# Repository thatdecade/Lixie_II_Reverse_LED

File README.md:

# Remix of Lixie II Open Hardware
Want to make your own Lixie II, but don't want to spend $$$$? You're in the right place. 

Based on the original work by Connor Nishijima: https://github.com/connornishijima/Lixie_II_OSHW

**Photo Album**
https://photos.app.goo.gl/PVswYqP2KvHP66T27

## Remix Notes
- PCB redrawn with a new BOM, using reverse mount LEDs. https://www.adafruit.com/product/4960
  - Loosely based on Adafruit's RGB NeoKey https://www.adafruit.com/product/5157
  - One capacitor per LED
  - Transmission resistors for stable data
- EPS files for lasercutting were converted to DXF.
- Laser Cut files have been redrawn for smaller runs.  
  - Ordering one set = One Digit of the Display
  - Ponoko wil auto-panelize larger orders together.
  - Be sure to read https://help.ponoko.com/en/articles/4405518-getting-started-with-ponoko
- 3D Printed versions of some of the lasercut files

|Filename|Supplier|Material|Thickness|
| ----------- | ----------- | ----------- | ----------- |
|BASEx2.dxf|Ponoko|Black Melamine MDF|6.4|
|NUM0-9.dxf|Ponoko|Clear Acrylic|1.5|
|DECIMAL.dxf|Ponoko|Gray Translucent Acrylic|3|
|LIGHTFILTER.dxf|Ponoko|6061-T6 Aluminum|1|

- LixieII_Price_Calculator.xlsx calculates the cost (including electronics) based on how many you would like to make.  
Here are some BOM estimates as of Oct 28, 2022:

|QTY|Total Cost|Cost Each|
| ----------- | ----------- | ----------- |
|1|$166|$166|
|2|$233|$117|
|4|$255|$64|
|8|$392|$49|
|10|$446|$45|
|16|$665|$42|
|32|$1250|$39|
|200|$4740|$24|

## Todo

- Convert Lightplate into pcb gerbers for cheaper cutting

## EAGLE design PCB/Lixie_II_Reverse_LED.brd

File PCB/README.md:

Here you will find the files for the PCB.  

To order the PCBs pre-assembled, visit [pcbshopper](https://pcbshopper.com/) and click the Assembly tab.  Then you can fill out the form and compare pricing from different assemblers.

## Files for assembly:

* Lixie_II_Reverse_LED_GERBERS.zip
* Lixie_II_Reverse_LED_BOM.xlsx
* Lixie_II_Reverse_LED_PLACEMENT.xlsx

## Notes:

* If you don't have EagleCAD to open the .brd/.sch files, you can use the free version of Autodesk Fusion 360 and download Eagle Free.
* I use eagle to generate the .dxf files, ensuring alignment between the pcb and other layers.  

## Generating the DXF Files
Example for LIGHTFILTER.dxf
1. Open the the .brd file in eagle
1. View>Layer Settings: 
> * Select None
> * Select only the LIGHTFILTER/ENGRAVING layers
3. File>Export>DXF: 
> * Name the output file: LIGHTFILTER.dxf
> * Unselect Fill areas
> * Unselect Use wire widths
> * Set Units to mm
> * Press OK

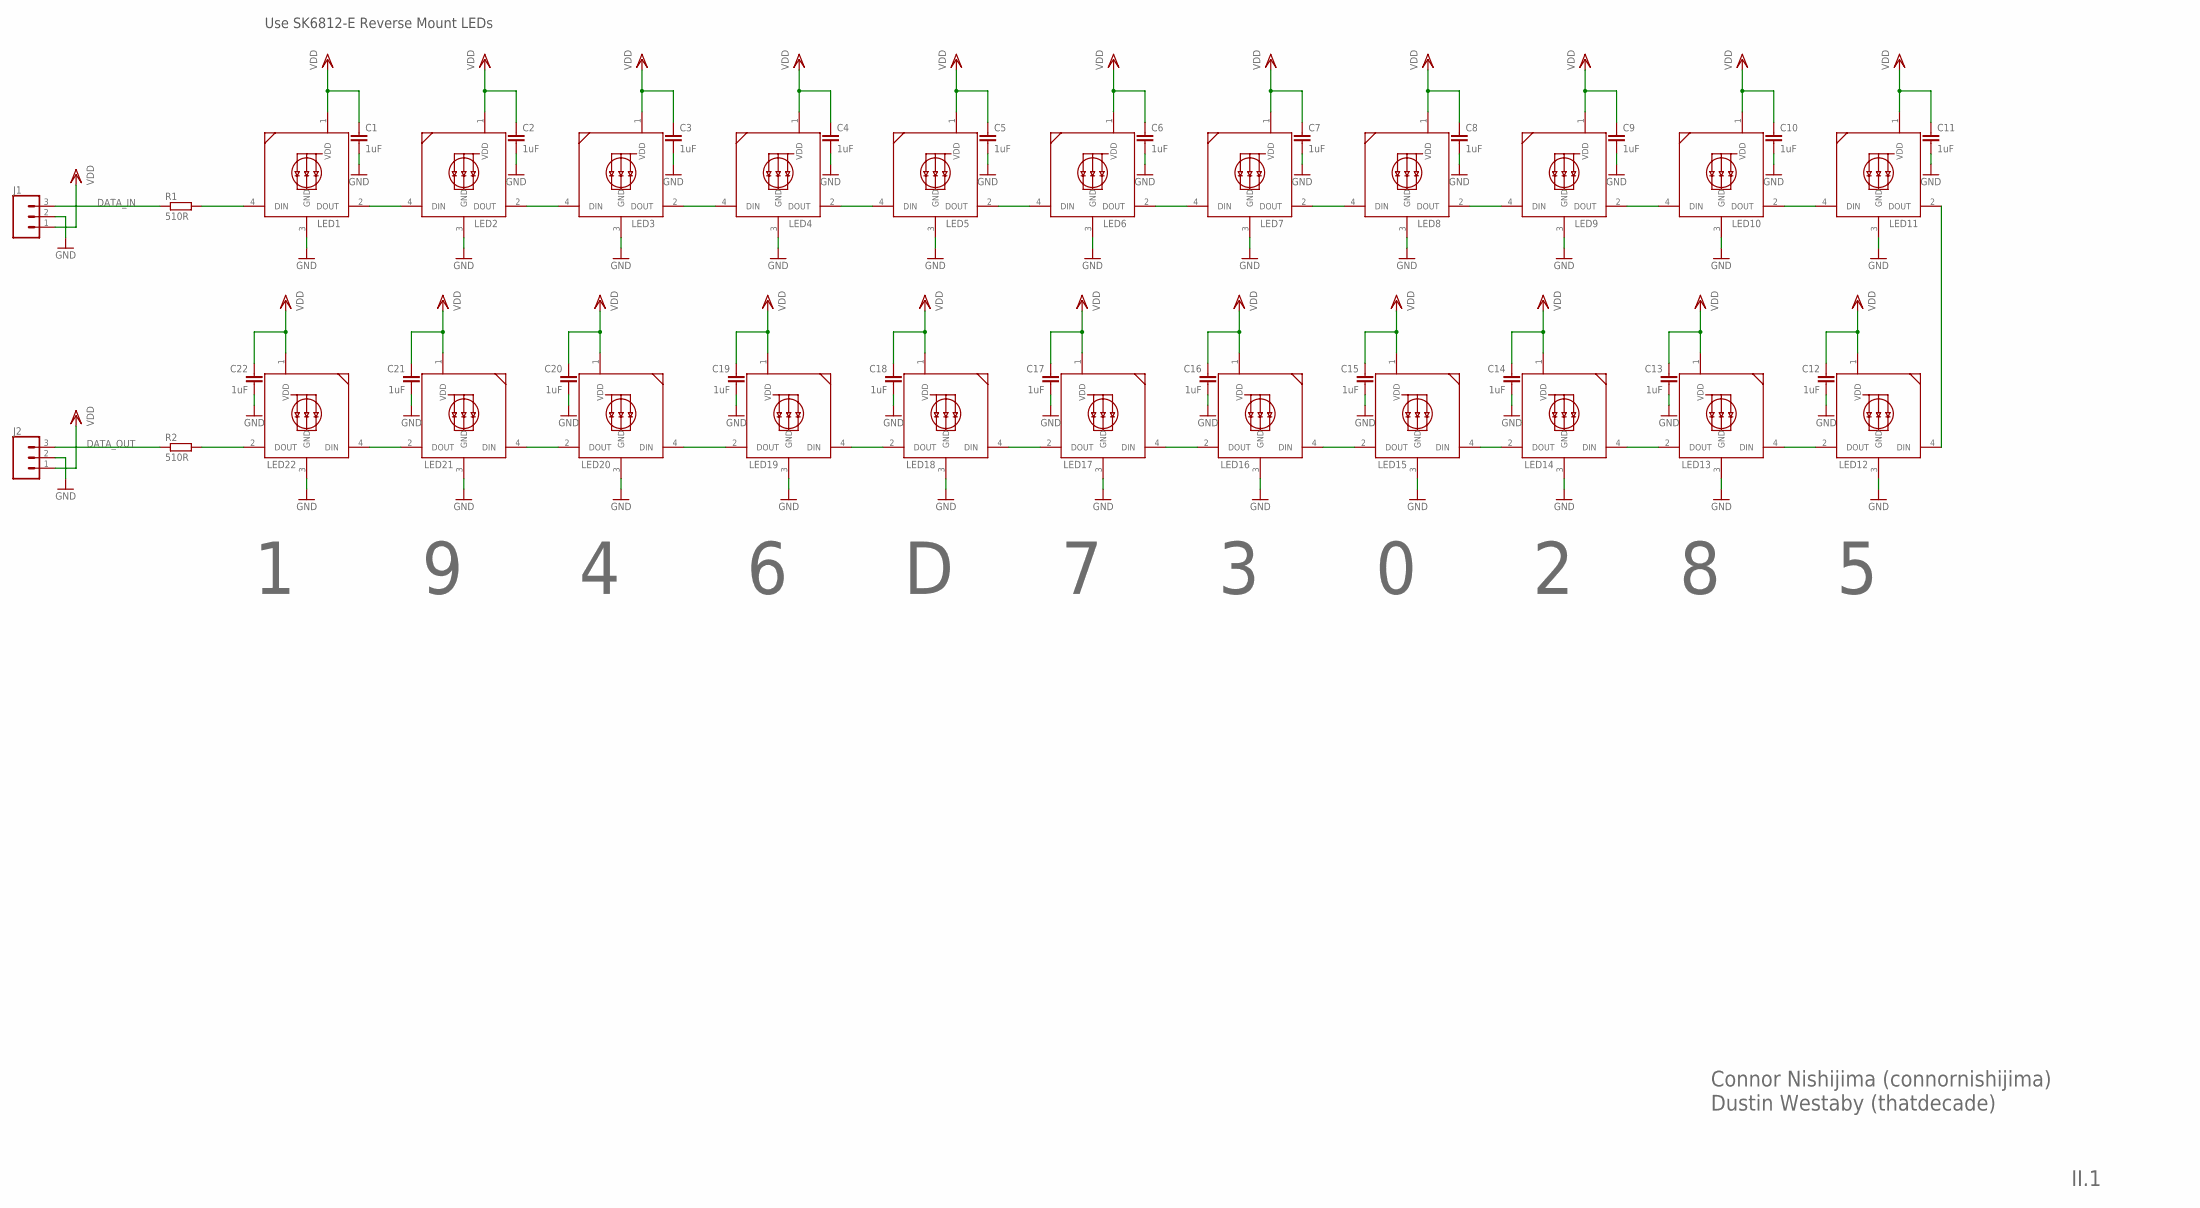
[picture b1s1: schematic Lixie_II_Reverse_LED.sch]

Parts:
C1, C2, C3, C4, C5, C6, C7, C8, C9, C10, C11, C12, C13, C14, C15, C16, C17, C18, C19, C20, C21, C22: 1uF; C0402
J1, J2: CONN_031X03_NO_SILK; 1X03_NO_SILK
LED1, LED2, LED3, LED4, LED5, LED6, LED7, LED8, LED9, LED10, LED11, LED12, LED13, LED14, LED15, LED16, LED17, LED18, LED19, LED20, LED21, LED22: SK6812MINI_REV; SK6812-E-SMD
R1, R2: 510R; R0402

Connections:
DATA_IN: J1.3, R1.1
DATA_OUT: J2.3, R2.1
GND: C1.2, C2.2, C3.2, C4.2, C5.2, C6.2, C7.2, C8.2, C9.2, C10.2, C11.2, C12.2, C13.2, C14.2, C15.2, C16.2, C17.2, C18.2, C19.2, C20.2, C21.2, C22.2, J1.2, J2.2, LED1.3 (GND), LED2.3 (GND), LED3.3 (GND), LED4.3 (GND), LED5.3 (GND), LED6.3 (GND), LED7.3 (GND), LED8.3 (GND), LED9.3 (GND), LED10.3 (GND), LED11.3 (GND), LED12.3 (GND), LED13.3 (GND), LED14.3 (GND), LED15.3 (GND), LED16.3 (GND), LED17.3 (GND), LED18.3 (GND), LED19.3 (GND), LED20.3 (GND), LED21.3 (GND), LED22.3 (GND)
unnamed: LED1.4 (DIN), R1.2
unnamed: LED11.2 (DOUT), LED12.4 (DIN)
unnamed: LED22.2 (DOUT), R2.2
unnamed: LED21.2 (DOUT), LED22.4 (DIN)
unnamed: LED20.2 (DOUT), LED21.4 (DIN)
unnamed: LED19.2 (DOUT), LED20.4 (DIN)
unnamed: LED18.2 (DOUT), LED19.4 (DIN)
unnamed: LED17.2 (DOUT), LED18.4 (DIN)
unnamed: LED16.2 (DOUT), LED17.4 (DIN)
unnamed: LED15.2 (DOUT), LED16.4 (DIN)
unnamed: LED14.2 (DOUT), LED15.4 (DIN)
unnamed: LED13.2 (DOUT), LED14.4 (DIN)
unnamed: LED12.2 (DOUT), LED13.4 (DIN)
unnamed: LED10.2 (DOUT), LED11.4 (DIN)
unnamed: LED9.2 (DOUT), LED10.4 (DIN)
unnamed: LED8.2 (DOUT), LED9.4 (DIN)
unnamed: LED7.2 (DOUT), LED8.4 (DIN)
unnamed: LED6.2 (DOUT), LED7.4 (DIN)
unnamed: LED5.2 (DOUT), LED6.4 (DIN)
unnamed: LED4.2 (DOUT), LED5.4 (DIN)
unnamed: LED3.2 (DOUT), LED4.4 (DIN)
unnamed: LED2.2 (DOUT), LED3.4 (DIN)
unnamed: LED1.2 (DOUT), LED2.4 (DIN)
VDD: C1.1, C2.1, C3.1, C4.1, C5.1, C6.1, C7.1, C8.1, C9.1, C10.1, C11.1, C12.1, C13.1, C14.1, C15.1, C16.1, C17.1, C18.1, C19.1, C20.1, C21.1, C22.1, J1.1, J2.1, LED1.1 (VDD), LED2.1 (VDD), LED3.1 (VDD), LED4.1 (VDD), LED5.1 (VDD), LED6.1 (VDD), LED7.1 (VDD), LED8.1 (VDD), LED9.1 (VDD), LED10.1 (VDD), LED11.1 (VDD), LED12.1 (VDD), LED13.1 (VDD), LED14.1 (VDD), LED15.1 (VDD), LED16.1 (VDD), LED17.1 (VDD), LED18.1 (VDD), LED19.1 (VDD), LED20.1 (VDD), LED21.1 (VDD), LED22.1 (VDD)

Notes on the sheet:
Dustin Westaby (thatdecade)
Connor Nishijima (connornishijima)
II.1
Use SK6812-E Reverse Mount LEDs

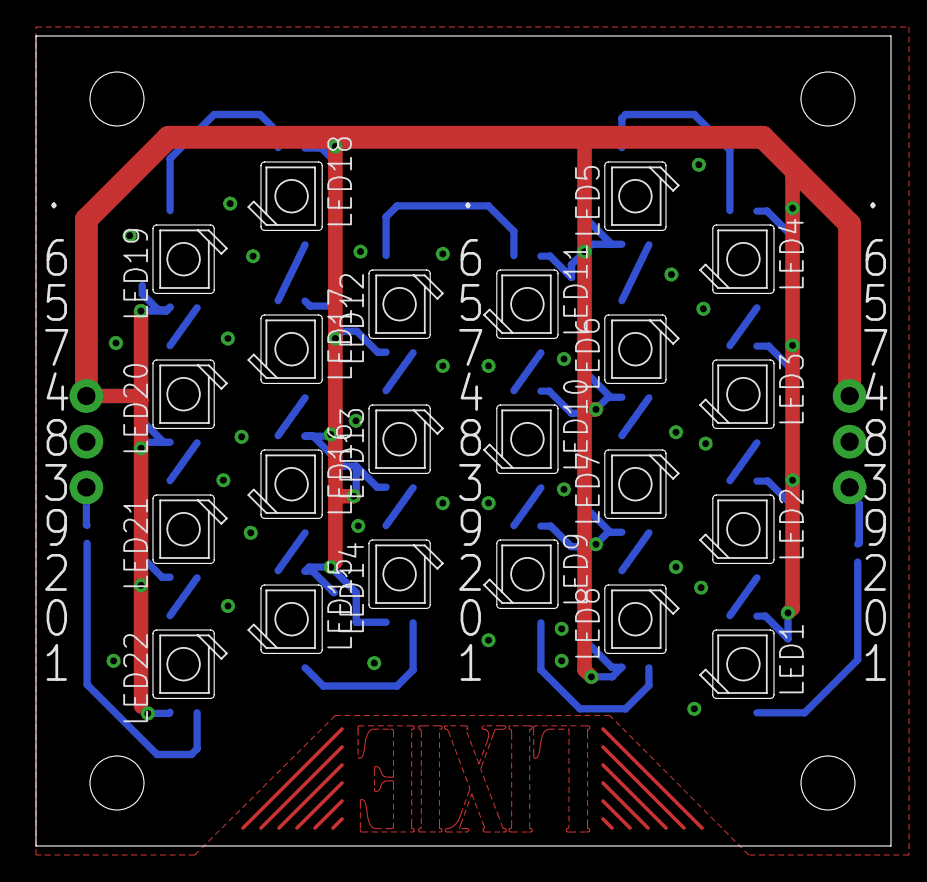
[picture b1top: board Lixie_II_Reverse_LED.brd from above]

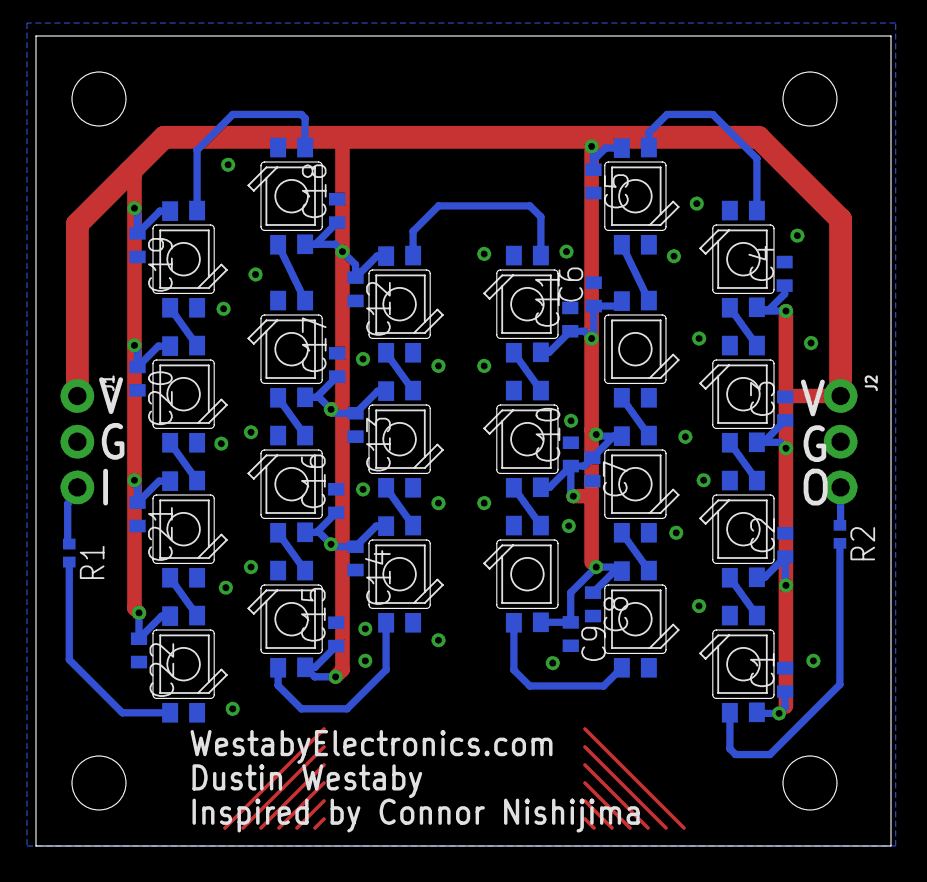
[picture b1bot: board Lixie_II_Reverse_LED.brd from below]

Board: 2 copper layers, 47.5 x 45.0 mm, 48 parts (26 on the bottom side), 27 nets.

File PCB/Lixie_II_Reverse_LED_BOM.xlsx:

Comment | Designator | Footprint | JLCPCB Part # | Value
Capacitor | C1 | C0603 | C15849 | 1uF
Capacitor | C2 | C0603 | C15849 | 1uF
Capacitor | C3 | C0603 | C15849 | 1uF
Capacitor | C4 | C0603 | C15849 | 1uF
Capacitor | C5 | C0603 | C15849 | 1uF
Capacitor | C6 | C0603 | C15849 | 1uF
Capacitor | C7 | C0603 | C15849 | 1uF
Capacitor | C8 | C0603 | C15849 | 1uF
Capacitor | C9 | C0603 | C15849 | 1uF
Capacitor | C10 | C0603 | C15849 | 1uF
Capacitor | C11 | C0603 | C15849 | 1uF
Capacitor | C12 | C0603 | C15849 | 1uF
Capacitor | C13 | C0603 | C15849 | 1uF
Capacitor | C14 | C0603 | C15849 | 1uF
Capacitor | C15 | C0603 | C15849 | 1uF
Capacitor | C16 | C0603 | C15849 | 1uF
Capacitor | C17 | C0603 | C15849 | 1uF
Capacitor | C18 | C0603 | C15849 | 1uF
Capacitor | C19 | C0603 | C15849 | 1uF
Capacitor | C20 | C0603 | C15849 | 1uF
Capacitor | C21 | C0603 | C15849 | 1uF
Capacitor | C22 | C0603 | C15849 | 1uF
Resistor | R1 | R0402 | C25123 | 510R
Resistor | R2 | R0402 | C25123 | 510R
Connector | J1 | 1X03_NO_SILK |  | 1x3
Connector | J2 | 1X03_NO_SILK |  | 1x3
Reverse Mount LED | LED1 | SK6812-E-SMD |  | SK6812MINI_REV
Reverse Mount LED | LED2 | SK6812-E-SMD |  | SK6812MINI_REV
Reverse Mount LED | LED3 | SK6812-E-SMD |  | SK6812MINI_REV
Reverse Mount LED | LED4 | SK6812-E-SMD |  | SK6812MINI_REV
Reverse Mount LED | LED5 | SK6812-E-SMD |  | SK6812MINI_REV
Reverse Mount LED | LED6 | SK6812-E-SMD |  | SK6812MINI_REV
Reverse Mount LED | LED7 | SK6812-E-SMD |  | SK6812MINI_REV
Reverse Mount LED | LED8 | SK6812-E-SMD |  | SK6812MINI_REV
Reverse Mount LED | LED9 | SK6812-E-SMD |  | SK6812MINI_REV
Reverse Mount LED | LED10 | SK6812-E-SMD |  | SK6812MINI_REV
Reverse Mount LED | LED11 | SK6812-E-SMD |  | SK6812MINI_REV
Reverse Mount LED | LED12 | SK6812-E-SMD |  | SK6812MINI_REV
Reverse Mount LED | LED13 | SK6812-E-SMD |  | SK6812MINI_REV
Reverse Mount LED | LED14 | SK6812-E-SMD |  | SK6812MINI_REV
Reverse Mount LED | LED15 | SK6812-E-SMD |  | SK6812MINI_REV
Reverse Mount LED | LED16 | SK6812-E-SMD |  | SK6812MINI_REV
Reverse Mount LED | LED17 | SK6812-E-SMD |  | SK6812MINI_REV
Reverse Mount LED | LED18 | SK6812-E-SMD |  | SK6812MINI_REV
Reverse Mount LED | LED19 | SK6812-E-SMD |  | SK6812MINI_REV
Reverse Mount LED | LED20 | SK6812-E-SMD |  | SK6812MINI_REV
Reverse Mount LED | LED21 | SK6812-E-SMD |  | SK6812MINI_REV
Reverse Mount LED | LED22 | SK6812-E-SMD |  | SK6812MINI_REV

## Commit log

2022-12-05 updated customizer for better splits and glue tabs
    also fixes issue #4 with parameterized window size.
2022-12-13 Adjusted light filter and base alignments
    Fixes issues #1 #2 #3
2022-12-13 Adjust window sizes and wire connector placement
    Narrow the windows to prevent light leaks, open on the sides to prevent short circuits
2022-12-13 Moved slots slightly to align with PCB
    Fixes issue #2
2022-12-15 Base part with threaded inserts
    3D printable base part with M3 heat set inserts.
2022-12-15 3D printable BASE
2022-12-15 Moves slots to align with PCB
2022-12-15 Rotated digits 5-9 to fixes issue #5
    Rotated digits 5-9 to fix orientation of chamfered edge
2022-12-16 Updated bom and adjusted connector position
2022-12-20 removed rogue cut path
2025-02-17 readme image
2025-02-17 Added image to readme

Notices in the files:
parts and their libraries:
SparkFun-Connectors: Licensing: Creative Commons ShareAlike 4.0 International - https://creativecommons.org/licenses/by-sa/4.0
